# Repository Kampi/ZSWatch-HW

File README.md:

# ZSWatch-HW

## Table of Contents

- [ZSWatch-HW](#zswatch-hw)
  - [Table of Contents](#table-of-contents)
  - [About](#about)
  - [Directory structure](#directory-structure)
  - [Developing](#developing)
  - [Maintainer](#maintainer)

## About

Hardware project for the [ZSWatch project](https://github.com/jakkra/ZSWatch/tree/main).

## Directory structure

- `cad`: 3D model of the complete PCB
- `docs`: All kind of project documentation like schematics, BOM, etc.
  - `drawings`: 2D drawings for subcomponents, etc.
  - `images`:
- `production`: Production files for the PCB
  - `PCBWay`: Ordering instructions and production files ready for ordering at [PCBWay](https://www.pcbway.com/)
- `project`: KiCad project for the PCB

## Developing

We recommend using our [KiCad](https://github.com/Kampi/KiCad) library when working on the PCB. The library contains all neccessary symbols, footprints and 3D models.

## Maintainer

- [Daniel Kampert](mailto:daniel.kameprt@kampis-elektroecke.de)
- [Jakob Krantz](mail@jakobkrantz.se)

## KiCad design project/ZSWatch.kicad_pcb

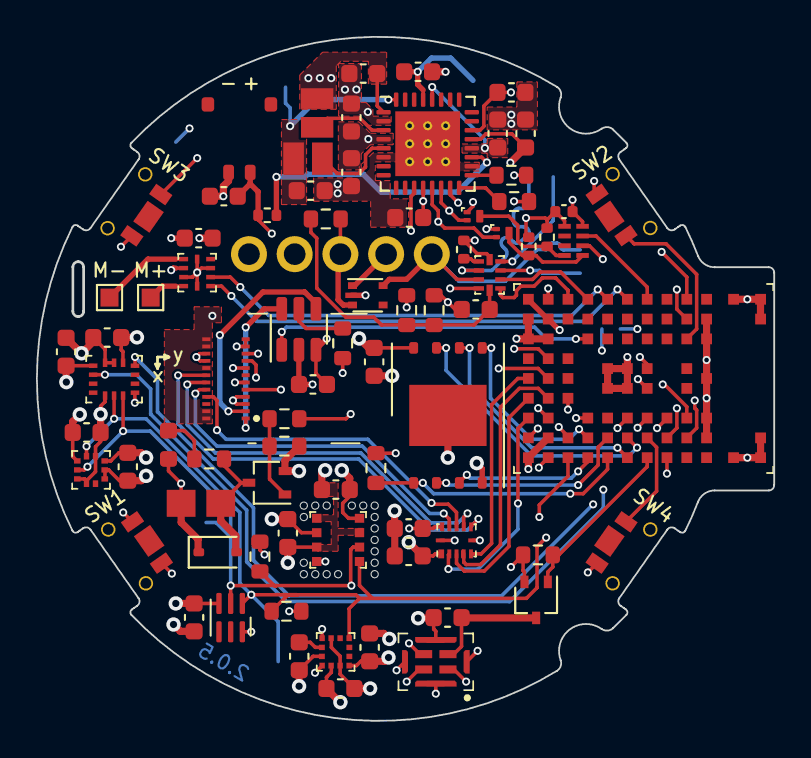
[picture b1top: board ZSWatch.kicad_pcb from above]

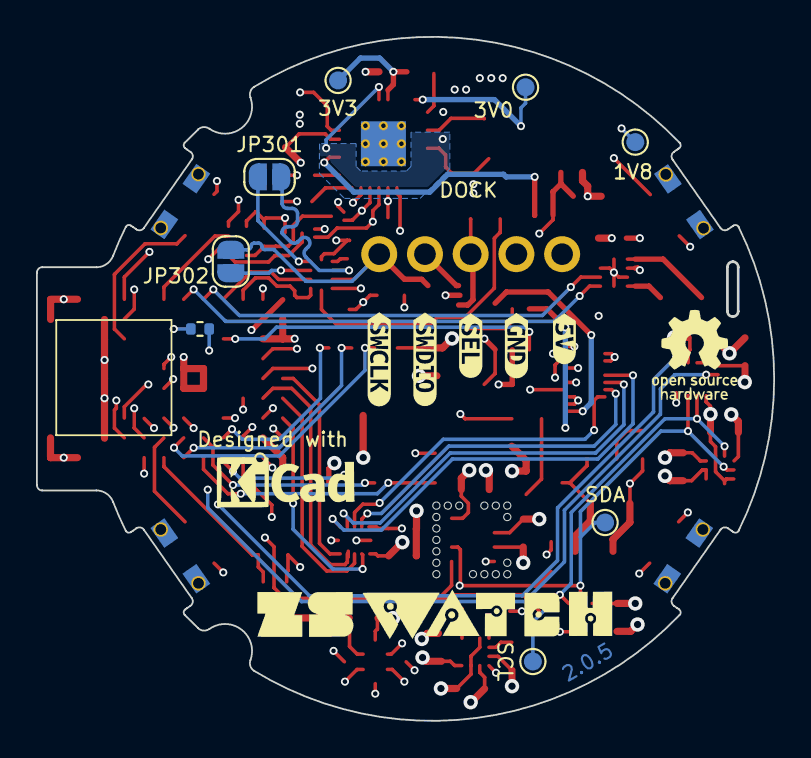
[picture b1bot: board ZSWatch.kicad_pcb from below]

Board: 4 copper layers, 41.0 x 38.0 mm, 91 parts (14 on the bottom side), 73 nets.

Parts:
BZ301: Buzzer; CMT-322-65-SMT-TR
C101, C110, C301: 1u; C_0603_1608Metric
C102, C201, C202, C203, C204, C206, C207, C210, C211, C212, C302, C303, C304, C305, C306: 100n; C_0603_1608Metric
C103: 2u2; C_0603_1608Metric
C104, C105, C106, C107, C108, C109, C209: 10u; C_0603_1608Metric
C208: 220n; C_0603_1608Metric
C307: 100n; C_0402_1005Metric
D301: BAS316; D_SOD-323
D302: LED_0603_1608Metric
IC101: nPM1300-QEXX; QFN-32-1EP_5x5mm_P0.5mm_EP3.6x3.6mm_ThermalVias
IC201: APDS-9306-065; Broadcom_DFN-6_2x2mm_P0.65mm
IC202: BMI270; Bosch_LGA-14_3x2.5mm_P0.5mm_LayoutBorder3x4y
IC203: BMP581; Bosch_LGA-10_2x2mm_P0.5mm_ClockwisePinNumbering
IC204: LIS2MDLTR; LGA-12_2x2mm_P0.5mm
IC205: BME688; Bosch_LGA-8_3x3mm_P0.8mm_ClockwisePinNumbering
IC301: ESDALC6V1W5; SOT-665
IC302: FAN5622SX; TSOT-23-6
IC303: MX25U51245GZ4I00; WSON-8-1EP_8x6mm_P1.27mm_EP3.4x4.3mm
IC304: TS3USB221A; UQFN-10_1.55x2.05mm_P0.5mm
IC305: NTS0104GU12; XQFN-12-1.7x2mm_P0.4mm
IC306: DRV2603RUNT; WQFN-10_2x2mm_P0.5mm
IC307: RV-8263-C8
JP301, JP302: SolderJumper-2_P1.3mm_Open_RoundedPad1.0x1.5mm
L101, L102: 2u2; L_0806_2016
M301: NORA-B106
MK201: SPK0641HT4H-1
Q201: DMG1013UW-7; SOT-323_SC-70
Q301: BC817W; SOT-323_SC-70
Q302, Q303: PMZ550UNEYL; SOT-883
R101: 47k; R_0603_1608Metric
R102, R201, R307: 150k; R_0603_1608Metric
R103, R306, R310: 0R; R_0402_1005Metric
R301: 12k; R_0603_1608Metric
R302, R305: 100k; R_0603_1608Metric
R303, R304: 4k7; R_0603_1608Metric
R308: 270R; R_0603_1608Metric
R309, R313: 4k7; R_0402_1005Metric
R311: 180R; R_0603_1608Metric
R312: 100R; R_0603_1608Metric
R314: 220R; R_0603_1608Metric
S301: SW1; TL6340AF160Q_Modified
S302: SW2; TL6340AF160Q_Modified
S303: SW3; TL6340AF160Q_Modified
S304: SW4; TL6340AF160Q_Modified
TP101: 1V8; TestPoint_Pad_D1.0mm
TP102: 3V0; TestPoint_Pad_D1.0mm
TP103: 3V3; TestPoint_Pad_D1.0mm
TP201: SCL; TestPoint_Pad_D1.0mm
TP202: SDA; TestPoint_Pad_D1.0mm
X101: BATTERY; 78171-0002
X301: DOCK; RD90_LZH0230529-004_DJ-5PIN_PH2_54
X302: GC9A01A_CST816S; ER-CON0.4-24P
X303: M+; TestPoint_Pad_1.0x1.0mm
X304: M-; TestPoint_Pad_1.0x1.0mm
kibuzzard-6616D313: G***; kibuzzard-6616D313
kibuzzard-656642B5: G***; kibuzzard-656642B5
kibuzzard-656642E4: G***; kibuzzard-656642E4
kibuzzard-65664337: G***; kibuzzard-65664337
kibuzzard-65664342: G***; kibuzzard-65664342

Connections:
+1V8: C102.1, C107.1, C201.1, C202.1, C203.2, C206.2, C207.1, C209.1, C210.1, C211.1, C212.2, C302.1, C304.1, IC101.1 (VOUT1), IC101.12 (VDDIO), IC201.3 (VDD), IC202.5 (VDDIO), IC202.8 (VDD), IC202.12 (CSB), IC203.1 (VDDIO), IC203.5 (SDO), IC203.6 (CSB), IC203.10 (VDD), IC204.3 (CS), IC204.9 (VDD), IC204.10 (VDDIO), IC205.2 (CSB), IC205.6 (VDDIO), IC205.8 (VDD), IC303.8 (VCC), IC305.1 (VCCA), L102.1, M301.A7 (VDD), M301.A8 (VDDH), M301.B7 (VDD), MK201.3 (SEL), Q201.2 (S), Q302.1 (G), Q303.1 (G), R201.2, R302.1, R303.1, R304.1, TP101.1, X302.11 (VDDIO), X302.12 (VDDIO)
+3V0: BZ301.1 (+), C105.1, D301.1 (K), D302.2 (A), IC101.32 (VOUT2), L101.1, TP102.1
/MCU/BMI270-INT1: IC202.4 (INT1), M301.G5 (P1.08)
/MCU/BMI270-INT2: IC202.9 (INT2), M301.G4 (P1.04)
/MCU/LIS2MDL-INT: IC204.7 (INT/DRDY), M301.H1 (P0.24)
/MCU/MIC-CLK: M301.F3 (P0.19), MK201.2 (CLK)
/MCU/MIC-DATA: M301.G3 (P0.25/AIN4), MK201.1 (DATA)
/MCU/MIC-EN: M301.G1 (P1.06), Q201.1 (G), R201.1
/MCU/PMIC-INT: IC101.11 (GPIO4), M301.J8 (P0.28/AIN7)
/MCU/SENSOR-SCL: IC101.14 (SCL), IC201.1 (SCL), IC202.13 (SCK), IC203.2 (SCK), IC204.1 (SCL/SPC), IC205.4 (SCK), M301.D3 (P0.07/AIN3), Q302.2 (S), R304.2, TP201.1
/MCU/SENSOR-SDA: IC101.13 (SDA), IC201.2 (SDA), IC202.14 (SDI), IC203.4 (SDI), IC204.4 (SDA/SDI/SDO), IC205.3 (SDI), M301.C1 (P0.10/TRACEDATA[1]), Q303.2 (S), R303.2, TP202.1
/MCU/VBAT: C103.1, C307.1, IC307.5 (VDD), R103.1, R309.1, R313.1, X101.1
/MCU/VBUS-MCU: C110.1, IC101.22 (VBUSOUT), M301.B9 (VBUS), R312.1
/MCU/VDD-Display: C108.1, C301.2, C305.1, IC101.29 (LSOUT1/VOUTLDO1), IC302.3 (VIN), IC305.11 (VCCB), TP103.1, X302.13 (VDD), X302.14 (VDD), X302.17 (CTP-VDD), X302.23 (LEDA2), X302.24 (LEDA1)
/MCU/VSYS: C104.1, C106.1, C109.1, C306.1, IC101.4 (PVDD), IC101.20 (VSYS), IC101.28 (LSIN1/VINLDO1), IC306.7 (VDD)
/MCU/V_SWITCH: C303.1, IC304.10 (VDD), R305.1, R308.1, R312.2
BTN-1: M301.H3 (P0.27/AIN6), S301.1
BTN-2: M301.J7 (P1.10), S302.2
BTN-3: IC101.15 (SHPHLD), M301.J9 (P0.31), S303.2
BTN-4: M301.G2 (P0.26/AIN5), S304.1
BUZZER: M301.B6 (P0.01/XL2), R311.1
DISPLAY-BLK: IC302.1 (CTRL), M301.D7 (P0.23)
DISPLAY-CLK: M301.C2 (P0.09/TRACEDATA[2]), X302.8 (SCL)
DISPLAY-CS: M301.A2 (P0.12/TRACECLK), X302.9 (CS)
DISPLAY-DATA: M301.B1 (P0.08/TRACEDATA[3]), X302.6 (SDI/SDA)
DISPLAY-DC: M301.B3 (P0.11/TRACEDATA[0]), X302.5 (RS/DC)
DISPLAY-EN: IC305.12 (OE), M301.C4 (P1.01)
DISPLAY-RST: M301.B5 (P0.03/NFC2), X302.10 (RESET)
D_N/SWDIO: IC301.1 (I/01), IC304.7 (D-), JP301.1 (A), X301.2
D_P/SWDCLK: IC301.5 (I/04), IC304.8 (D+), JP302.1 (A), X301.1
GND: C101.2, C102.2, C103.2, C104.2, C105.2, C106.2, C107.2, C108.2, C109.2, C110.2, C201.2, C202.2, C203.1, C204.2, C206.1, C207.2, C208.2, C209.2, C210.2, C211.2, C212.1, C301.1, C302.2, C303.2, C304.2, C305.2, C306.2, C307.2, IC101.2 (PVSS1), IC101.6 (PVSS2), IC101.18 (NTC), IC101.33 (AVSS), IC201.6 (GND), IC202.1 (SDO), IC202.6 (GND), IC202.7 (GND), IC203.3 (GND), IC203.8 (GND), IC203.9 (GND), IC204.6 (GND), IC204.8 (GND), IC205.1 (GND), IC205.5 (SDO), IC205.7 (GND), IC301.2 (GND), IC302.2 (GND), IC303.4 (GND), IC303.9 (EP), IC304.5 (GND), IC305.6 (GND), IC306.3 (LRA/~ERM), IC306.5 (GND), IC306.8 (GND), IC306.10 (GND), IC307.2 (CLKOE), IC307.4 (GND), M301.A1 (GND), M301.A9 (GND), M301.B2 (GND), M301.B8 (GND), M301.E4 (GND), M301.E5 (GND), M301.F4 (GND), M301.F5 (GND), M301.K2 (GND), M301.K3 (GND), M301.K5 (GND), M301.K7 (GND), M301.K8 (GND), M301.L1 (GND), M301.L9 (GND), M301.M1 (GND), M301.M2 (GND), M301.M8 (GND), M301.M9 (GND), MK201.5 (GND), MK201.6 (GND), MK201.7 (GND), MK201.8 (GND), Q301.2 (E), R101.1, R102.1, R301.1, R307.1, R308.2, R310.2, S301.2, S302.1, S303.1, S304.2, X101.2, X301.4, X302.3 (GND), X302.4 (GND), X302.15 (GND), X302.16 (GND)
LEDK1: IC302.6 (LED1), X302.1 (LEDK-1)
LEDK2: IC302.4 (LED2), X302.2 (LEDK-2)
unnamed: BZ301.2 (-), D301.2 (A), Q301.3 (C), R314.2
unnamed: D302.1 (K), R314.1
unnamed: IC101.3 (SW1), L102.2
unnamed: IC101.5 (SW2), L101.2
unnamed: IC101.19 (VBAT), R103.2
unnamed: IC101.17 (VSET1), R101.2
unnamed: IC101.16 (VSET2), R102.2
unnamed: C208.1, IC204.5 (C1)
unnamed: IC302.5 (ISET), R301.2
unnamed: IC304.6 (~OE), R310.1
unnamed: IC305.10 (B1), X302.20 (CTP-SCL)
unnamed: IC305.9 (B2), X302.21 (CTP-INT)
unnamed: IC305.8 (B3), X302.19 (CTP-SDA)
unnamed: IC305.7 (B4), X302.18 (CTP-RST)
unnamed: IC306.9 (OUT+), X303.1
unnamed: IC306.6 (OUT-), X304.1
unnamed: IC307.8 (SCL), Q302.3 (D), R313.2
unnamed: IC307.1 (SDA), Q303.3 (D), R309.2
unnamed: C204.1, MK201.4 (VDD), Q201.3 (D)
unnamed: Q301.1 (B), R307.2, R311.2
QSPI-CLK: IC303.6 (SCK), M301.F1 (P0.17/QSPI_CLK)
QSPI-CS: IC303.1 (~CS), M301.E1 (P0.18/QSPI_CS), R302.2
QSPI-IO0: IC303.5 (SI(I/O0)), M301.D2 (P0.13/QSPI[0])
QSPI-IO1: IC303.2 (SO(I/O1)), M301.E2 (P0.14/QSPI[1])
QSPI-IO2: IC303.3 (~WP(I/O2)), M301.D1 (P0.15/QSPI[2])
QSPI-IO3: IC303.7 (~HOLD(I/O3)), M301.F2 (P0.16/QSPI[3])
RESETn: M301.J3 (~RESET), R306.2
SEL-SWD: IC301.3 (I/02), IC304.9 (S), R305.2, R306.1, X301.3
SWDCLK: IC304.3 (2D+), JP302.2 (B), M301.J2 (SWDCLK)
SWDIO: IC304.4 (2D-), JP301.2 (B), M301.H2 (SWDIO)
TOUCH-INT: IC305.3 (A2), M301.A4 (P1.00)
TOUCH-RST: IC305.5 (A4), M301.A5 (P0.20)
TOUCH-SCL: IC305.2 (A1), M301.A3 (P1.03/I2C)
TOUCH-SDA: IC305.4 (A3), M301.B4 (P1.02/I2C)
USB-D_N: IC304.2 (1D-), M301.D9 (D-)
USB-D_P: IC304.1 (1D+), M301.C9 (D+)
VBUS: C101.1, IC101.21 (VBUS), X301.5
VIB-EN: IC306.1 (EN), M301.F9 (P1.15)
VIB-PWM: IC306.2 (PWM), M301.E9 (P1.05)
nRTC-INT: IC307.3 (~INT), M301.G9 (P1.13)

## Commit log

2023-09-25 Initialize branch
2023-09-29 Working on USB test board
2023-10-02 Working on nPM1300 design
2023-10-04 First design for PCBWay
2023-10-06 Add additional jumper for SEL pin
2023-10-06 Add QSPI for flash
2023-10-10 Add note to schematics
2023-10-23 Add measurements from nPM1300
2023-10-25 VSET resistors need fix
2023-10-28 Working on nPM circuit
2023-11-05 Add missing output capacitor for LDO output
2024-02-07 Add image from CI/CD action
2024-05-27 Fix different manufacturing issues
2024-06-19 Update build.yml
    - Update upload-artifact to v4
    - Add git pull before pushing to prevent upload issues
2024-10-01 Change layer for PCB tables to User1
2024-11-07 Switch to KiBot container
2024-11-07 Remove update command
2024-11-07 Remove KiCad library from Kampi
2024-11-07 Remove dependencies step
